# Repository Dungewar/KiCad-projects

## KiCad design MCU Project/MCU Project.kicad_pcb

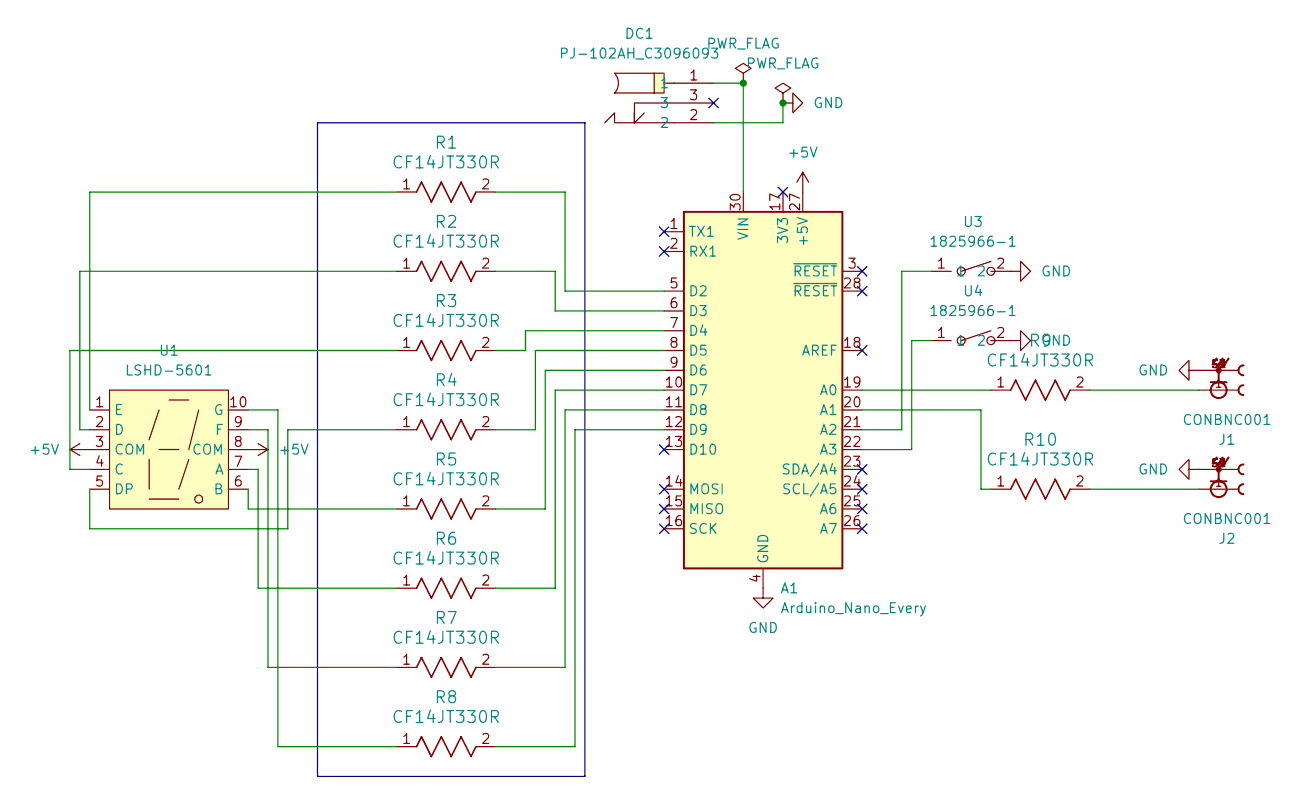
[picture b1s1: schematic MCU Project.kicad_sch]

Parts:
A1: Arduino_Nano_Every; Arduino_Nano
DC1: PJ-102AH_C3096093; DC-IN-TH_PJ-102AH; LCSC Part C3096093
J1, J2: CONBNC001; LINX_CONBNC001
R1, R2, R3, R4, R5, R6, R7, R8, R9, R10: CF14JT330R; STA_CF14_STP
U1: LSHD-5601; LED-SEG-TH_10P-L17.1-W12.4-P2.54-D0.3-LS15.24; LCSC Part C7217513
U3, U4: 1825966-1; SW-TH_L6.0-W3.6-P6.50; LCSC Part C5172268

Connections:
+5V: A1.27 (+5V), U1.3 (COM), U1.8 (COM)
GND: A1.4 (GND), A1.29 (GND), DC1.2, J1.S1, J1.S2, J1.S3, J1.S4, J2.S1, J2.S2, J2.S3, J2.S4, U3.2, U4.2
unnamed: A1.19 (A0), R9.1
unnamed: A1.20 (A1), R10.1
unnamed: A1.21 (A2), U3.1
unnamed: A1.22 (A3), U4.1
unnamed: A1.5 (D2), R1.2
unnamed: A1.6 (D3), R2.2
unnamed: A1.7 (D4), R3.2
unnamed: A1.8 (D5), R4.2
unnamed: A1.9 (D6), R5.2
unnamed: A1.10 (D7), R6.2
unnamed: A1.11 (D8), R7.2
unnamed: A1.12 (D9), R8.2
unnamed: A1.30 (VIN), DC1.1
unnamed: J1.1, R9.2
unnamed: J2.1, R10.2
unnamed: R6.1, U1.7 (A)
unnamed: R5.1, U1.6 (B)
unnamed: R3.1, U1.4 (C)
unnamed: R2.1, U1.2 (D)
unnamed: R4.1, U1.5 (DP)
unnamed: R1.1, U1.1 (E)
unnamed: R7.1, U1.9 (F)
unnamed: R8.1, U1.10 (G)

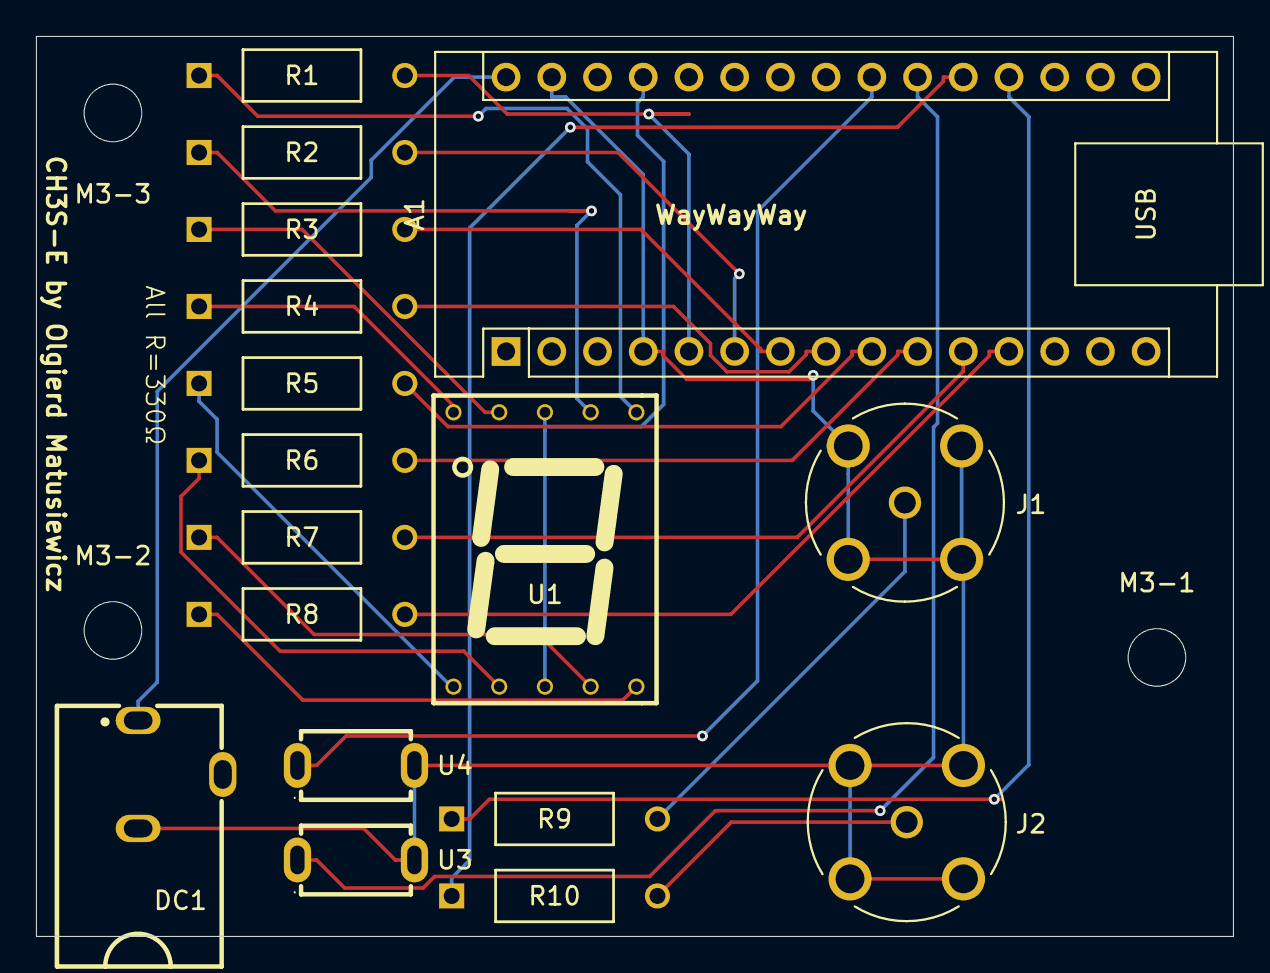
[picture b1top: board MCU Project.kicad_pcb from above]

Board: 2 copper layers, 66.5 x 50.0 mm, 20 parts (0 on the bottom side), 25 nets.

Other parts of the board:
M3-1, M3-2, M3-3: MountingHole_3.2mm_M3

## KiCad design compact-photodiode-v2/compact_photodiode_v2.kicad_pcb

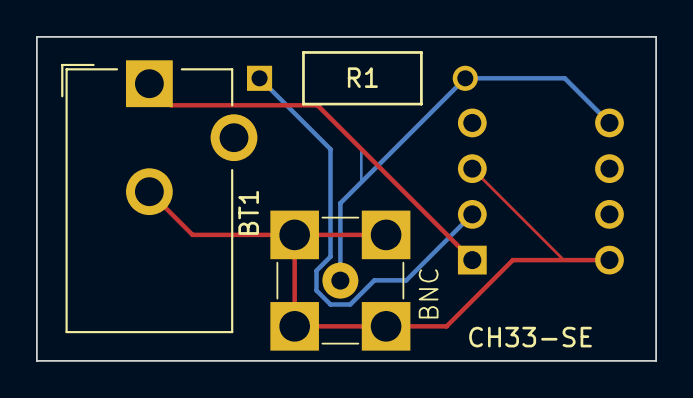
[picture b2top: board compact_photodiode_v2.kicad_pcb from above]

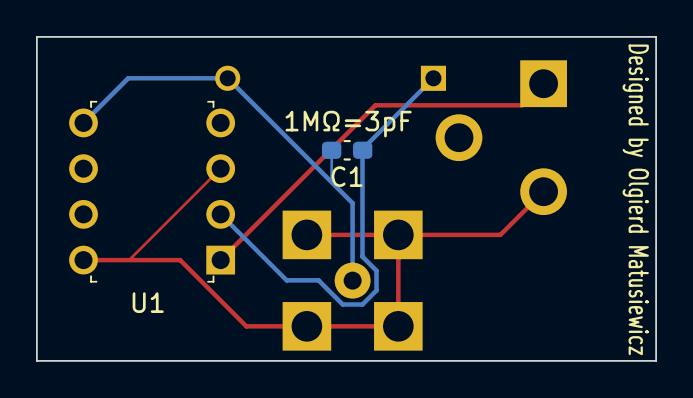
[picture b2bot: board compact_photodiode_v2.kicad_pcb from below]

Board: 2 copper layers, 34.4 x 18.0 mm, 5 parts (2 on the bottom side), 4 nets.

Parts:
BNC: SMB_Molex_0731000103_THT_RA
BT1: Battery_Cell; BarrelJack_CUI_PJ-102AH_Horizontal
C1: C; C_0603_1608Metric_Pad1.08x0.95mm_HandSolder
R1: CF14JT5M10; STA_CF14_STP
U1: OPT101P; DIP-8_W7.62mm

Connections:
+9V: BT1.1 (+), U1.1 (VS)
GND: BNC.1 (GND), BT1.2 (-), U1.3 (V-), U1.8 (COM)
unnamed: C1.2, R1.1, U1.2 (-IN)
unnamed: BNC.2 (IN), C1.1, R1.2, U1.5 (OUT)

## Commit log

2025-04-13 start project
2025-04-13 do something
2025-04-13 add library
2025-04-14 finish v2.1
2025-04-27 Add text
2026-01-08 Start MCU Project
2026-01-09 Do work
2026-01-09 Do soemthing
